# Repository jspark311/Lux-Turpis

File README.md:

# Lux Turpis ("Light Mixer")

Lux Turpis is an ISM radio relay. The hardware is a one-off multi-platform system
that is mounted to an antenna mast. You can try to replicate it if you like, but
it is being posted more as a demonstration and documentation piece, rather than as
a usable body of code and hardware plans.

----------------------
#### What is in this repository:

**./doc**:  Documentation related to this project.

**./lib**:  External dependencies.

**./src**:  Original (unless otherwise specified) source code.

----------------------
#### Write-up

[Pictures and more info](https://hackaday.io/project/167063-lux-turpis)

----------------------
#### License
Original code is Apache 2.0.

Code adapted from others' work inherits their license terms, which were preserved in the commentary where it applies.

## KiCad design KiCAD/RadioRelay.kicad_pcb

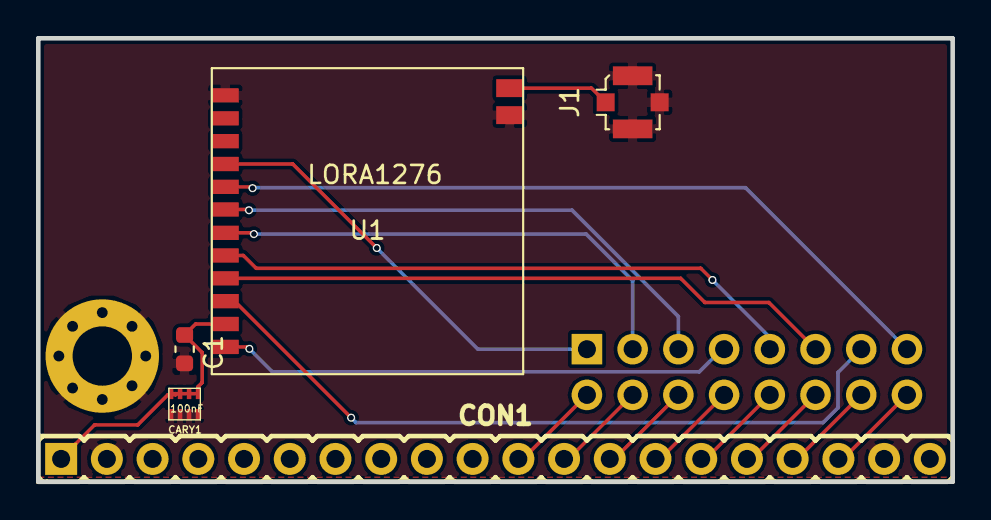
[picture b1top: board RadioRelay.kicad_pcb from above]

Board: 2 copper layers, 50.8 x 24.6 mm, 8 parts (1 on the bottom side), 19 nets.

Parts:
C1: 10uF; C_0603_1608Metric
CARY1: 100nF; CapArray_CKCL44
CON1: Conn_01x20; HN1x20
J1: Conn_Coaxial; U.FL_Molex_MCRF_73412-0110_Vertical
J2: Conn_02x08_Odd_Even; PinHeader_2x08_P2.54mm_Vertical
MH1: Mounting_hole_Shield_3.3mm
P1: CONN_01X01; ManuvrLogo
U1: LORA1276; LORA1276-Module

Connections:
/3v3: C1.2, CARY1.1, CARY1.3, CARY1.5, CARY1.7, CON1.1, U1.11
/LORA_CS: J2.3, U1.7
/LORA_DIO0: J2.13, U1.10
/LORA_DIO1: J2.11, U1.9
/LORA_DIO2: J2.9, U1.8
/SPI1_CLK: J2.1, U1.4
/SPI1_MISO: J2.15, U1.5
/SPI1_MOSI: J2.5, U1.6
/~LORA_RESET: J2.7, U1.12
GND: C1.1, CARY1.2, CARY1.4, CARY1.6, CARY1.8, CON1.2, CON1.19, J1.2, MH1.GND1, U1.1, U1.13
unnamed: CON1.11, J2.2
unnamed: CON1.12, J2.4
unnamed: CON1.13, J2.6
unnamed: CON1.14, J2.8
unnamed: CON1.15, J2.10
unnamed: CON1.16, J2.12
unnamed: CON1.17, J2.14
unnamed: CON1.18, J2.16
unnamed: J1.1, U1.14

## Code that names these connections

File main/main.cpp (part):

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#define SDA_PIN             14  // IO14
#define SCL_PIN             15  // IO15
#define SPI_CLK_PIN         16  // IO16
#define LORA_CS_PIN         17  // IO17
#define SPI_MOSI_PIN        32  // IO32
#define LORA_RESET_PIN      33  // IO33
#define LORA_DIO2_PIN       34  // IO34
#define LORA_DIO1_PIN       35  // IO35
#define LORA_DIO0_PIN       36  // IO36
#define SPI_MISO_PIN        39  // IO39


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);

const SX1276Opts sx1276_opts(
  LORA_RESET_PIN,  // Reset
  LORA_CS_PIN,     // CS
  LORA_DIO0_PIN,   // D0
  LORA_DIO1_PIN,   // D1
  LORA_DIO2_PIN,   // D2
  LORABand::BAND_915
);

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
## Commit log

2019-08-11 Adding first semi-operational boilerplate.
2019-12-22 Build fix. Addition of GPIO expander.
2021-10-31 Sync commit.
2021-10-31 Updating build system.
2021-10-31 Adding more build trim.
2021-10-31 PHY support has changed beyond recognition.
2022-10-09 Keeping pace with C3P, but this probably won't build. It is about to be updated massively.
2022-10-09 About to re-write the ISM module.
2022-10-09 Build works again.
2022-10-09 Removal of old source and datasheets.
2022-10-30 Compiles again.
2022-11-13 LoRa console migration. Adding Raspi setup doc.
2022-11-24 Adding datasheet.
